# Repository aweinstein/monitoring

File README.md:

# monitoring
Monitoring environmental variables

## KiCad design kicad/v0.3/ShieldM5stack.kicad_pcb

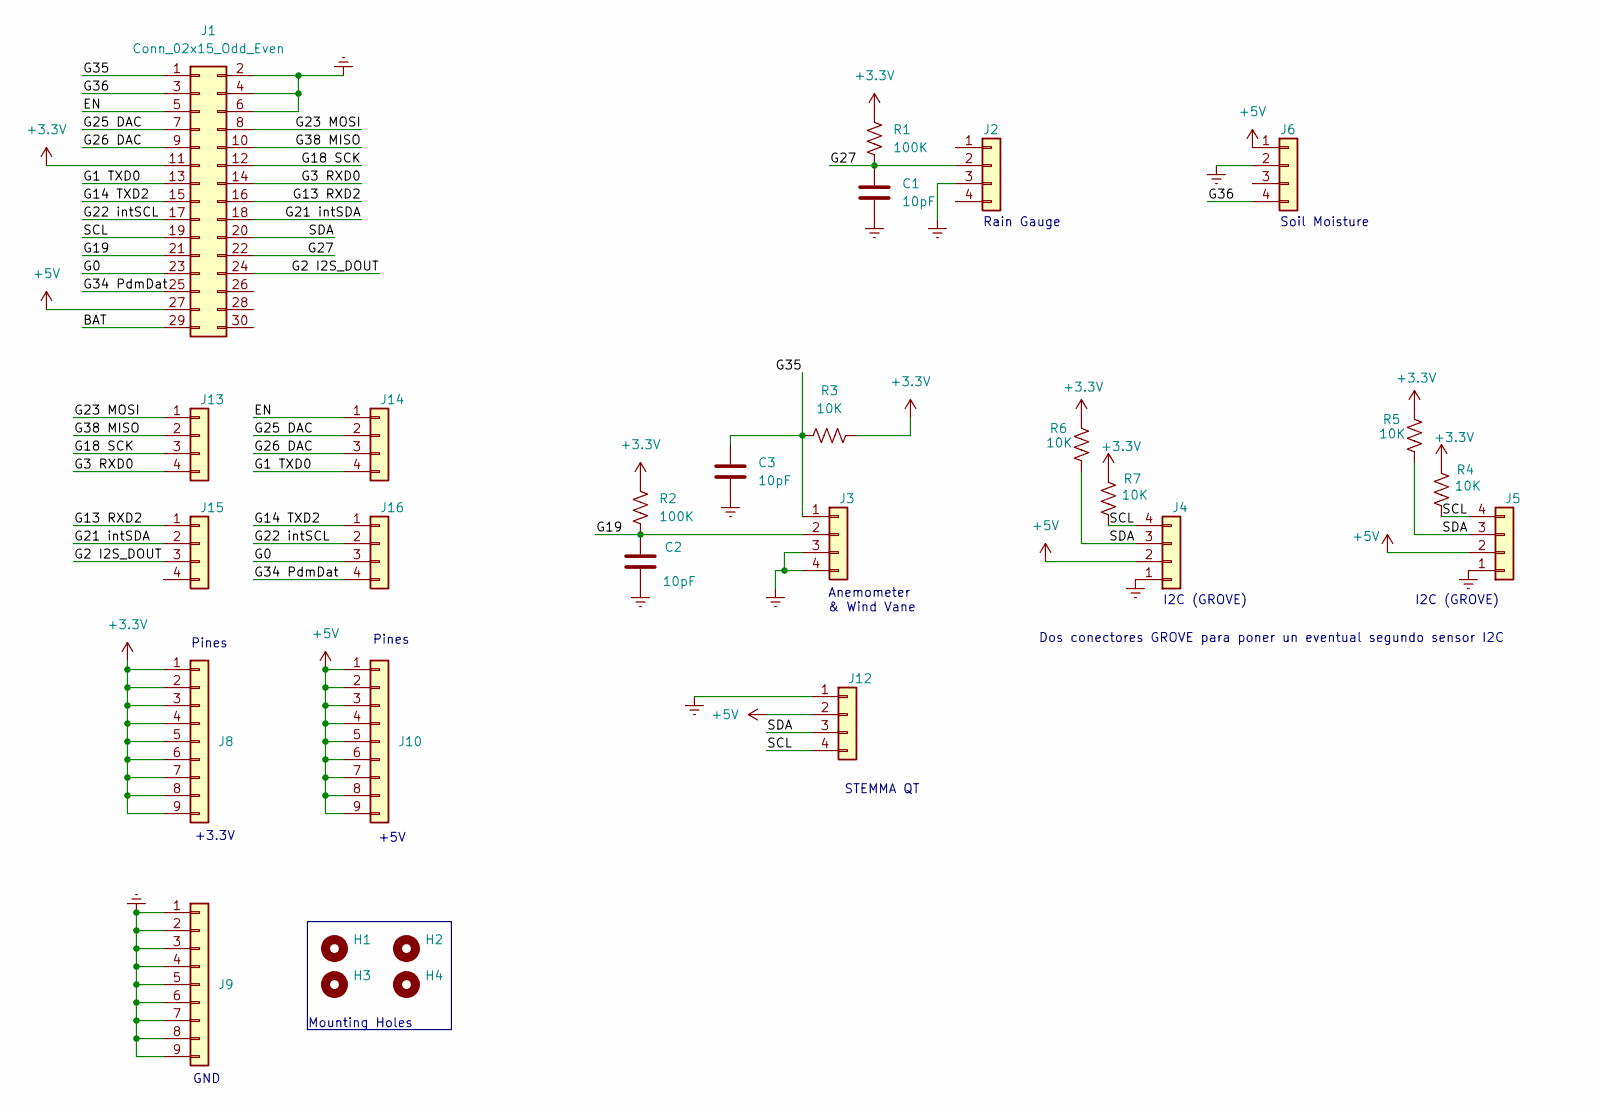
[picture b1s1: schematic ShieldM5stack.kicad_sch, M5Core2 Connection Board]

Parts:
C1, C2, C3: 10pF; C_0805_2012Metric
H1, H2, H3, H4: MountingHole; MountingHole_3mm
J1: Conn_02x15_Odd_Even; PinHeader_2x15_P2.54mm_Vertical
J2, J3, J6: Conn_01x04; RJ12_Amphenol_54601-x06_Horizontal
J4, J5: Conn_01x04; NS-Tech_Grove_1x04_P2mm_Vertical
J8, J9, J10: Conn_01x09; PinHeader_1x09_P2.54mm_Vertical
J12, J13, J14, J15, J16: Conn_01x04; PinHeader_1x04_P2.54mm_Vertical
R1, R2: 100K; R_0805_2012Metric
R3, R4, R5, R6, R7: 10K; R_0805_2012Metric

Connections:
+3.3V: J1.11, J8.1, J8.2, J8.3, J8.4, J8.5, J8.6, J8.7, J8.8, J8.9, R1.1, R2.1, R3.2, R4.1, R5.1, R6.1, R7.1
+5V: J1.27, J4.2, J5.2, J6.1, J10.1, J10.2, J10.3, J10.4, J10.5, J10.6, J10.7, J10.8, J10.9, J12.2
/BAT: J1.29
/EN: J1.5, J14.1
/G0: J1.23, J16.3
/G1 TXD0: J1.13, J14.4
/G2 I2S_DOUT: J1.24, J15.3
/G3 RXD0: J1.14, J13.4
/G13 RXD2: J1.16, J15.1
/G14 TXD2: J1.15, J16.1
/G18 SCK: J1.12, J13.3
/G19: C2.1, J1.21, J3.2, R2.2
/G21 intSDA: J1.18, J15.2
/G22 intSCL: J1.17, J16.2
/G23 MOSI: J1.8, J13.1
/G25 DAC: J1.7, J14.2
/G26 DAC: J1.9, J14.3
/G27: C1.1, J1.22, J2.2, R1.2
/G34 PdmDat: J1.25, J16.4
/G35: C3.1, J1.1, J3.1, R3.1
/G36: J1.3, J6.4
/G38 MISO: J1.10, J13.2
/SCL: J1.19, J4.4, J5.4, J12.4, R4.2, R7.2
/SDA: J1.20, J4.3, J5.3, J12.3, R5.2, R6.2
GNDREF: C1.2, C2.2, C3.2, J1.2, J1.4, J1.6, J2.3, J3.3, J3.4, J4.1, J5.1, J6.2, J9.1, J9.2, J9.3, J9.4, J9.5, J9.6, J9.7, J9.8, J9.9, J12.1

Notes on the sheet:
I2C (GROVE)
Mounting Holes
Rain Gauge
Soil Moisture
Pines
+5V
Anemometer & Wind Vane
GND
Dos conectores GROVE para poner un eventual segundo sensor I2C
STEMMA QT
+3.3V

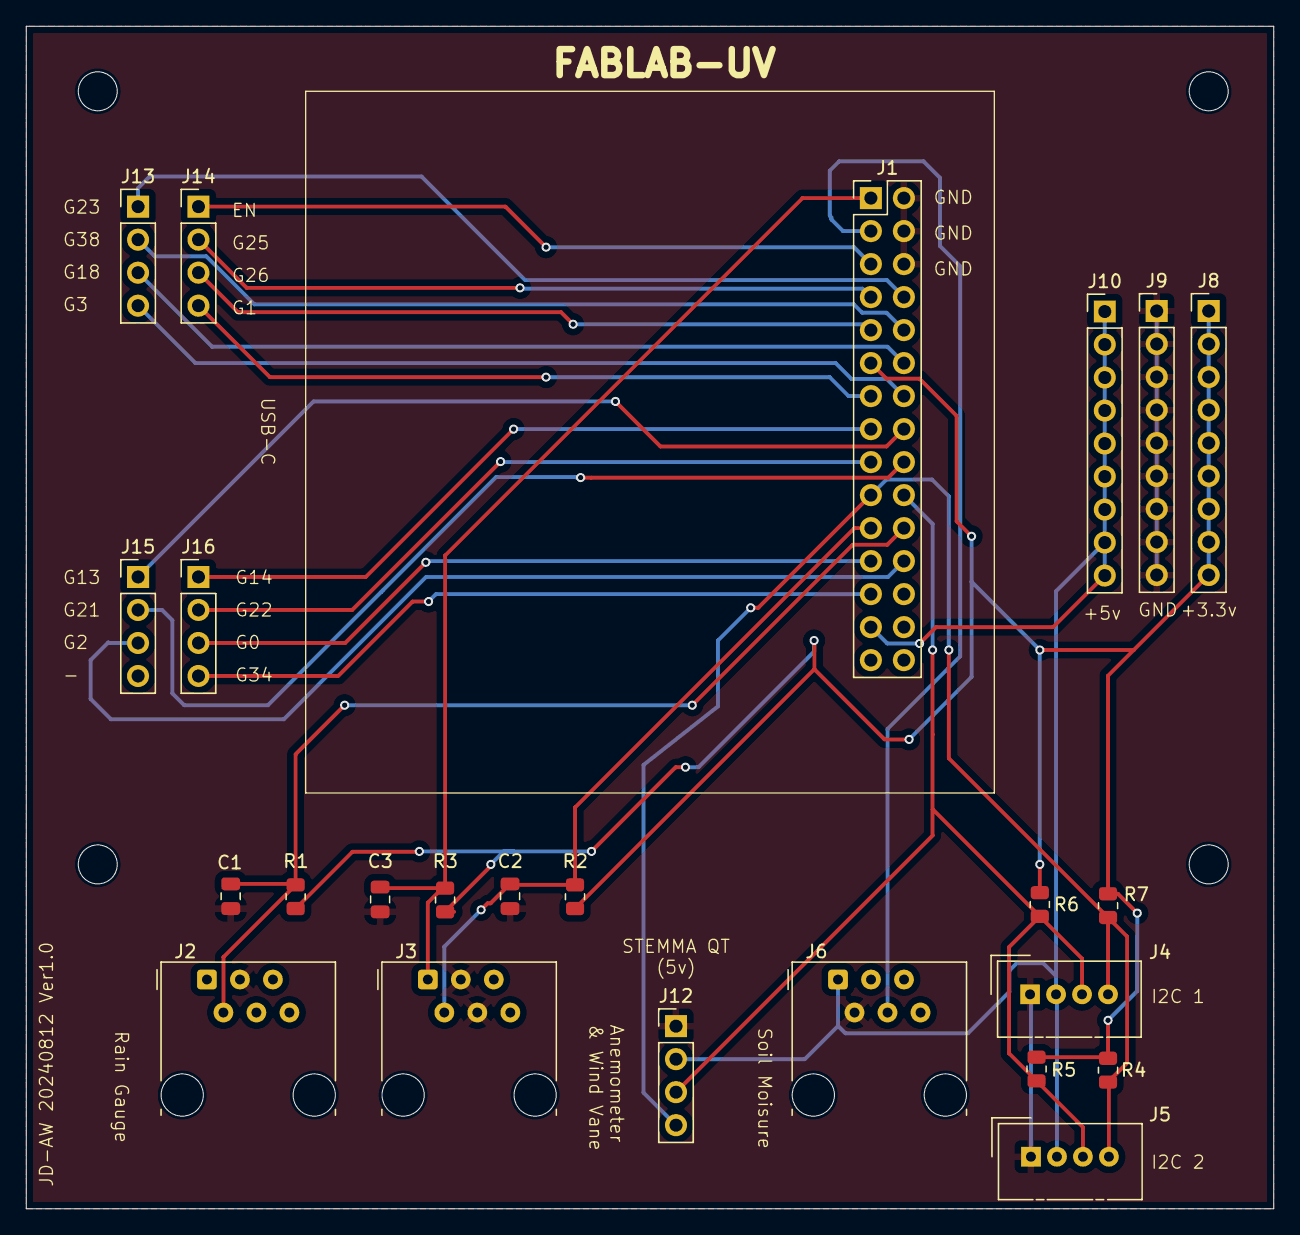
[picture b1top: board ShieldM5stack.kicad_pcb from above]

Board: 2 copper layers, 96.0 x 91.0 mm, 28 parts (0 on the bottom side), 24 nets.

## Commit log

2024-10-13 Initial upload of main folder
2024-10-14 Add main folder
2024-10-14 Add M5 extetension KiCad board
2024-10-14 Add initial BME280 reading display
2024-10-15 Add PDF with schematics and PCB.
2024-10-16 Implement sending data sent from sensors to network module
2024-10-17 Add debug compile mode (sensorless), REPL test
2024-10-25 Add BME280 sensor display, sending data from sensors, and initial REPL setup (#3)
    * Add initial BME280 reading display
    * Implement sending data sent from sensors to network module
    * Add debug compile mode (sensorless), REPL test
2024-10-28 Restructure code to use queues, in order to handle connection drops. Catch-up functionality using SD card pending
2024-10-28 Restructure code to use queues, in order to handle connection drops. Catch-up functionality using SD card pending (#4)
2025-01-08 Add data recovery function, RTC configuration (#5)
    * Refactor project structure to more clearly separate functionality
    * Added data recovery functionality to retrieve unsent data from SD card. Also, fixed a regression that broke SD storage completely (oops)
    * Add command to set RTC time, change commands to a more logical scheme (in my opinion)
    * Fix buffer being too small in readDataAndQueue function, also fix ntp timezone selection
    * Added debug data generation for BME280
    * Cleaned up repository
